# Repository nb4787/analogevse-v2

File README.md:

# analogevse-v2
AnalogEVSE Version 2

A fully analog J1772 compliant EV charge controller. For details go to the home page

http://www.analogevse.xyz

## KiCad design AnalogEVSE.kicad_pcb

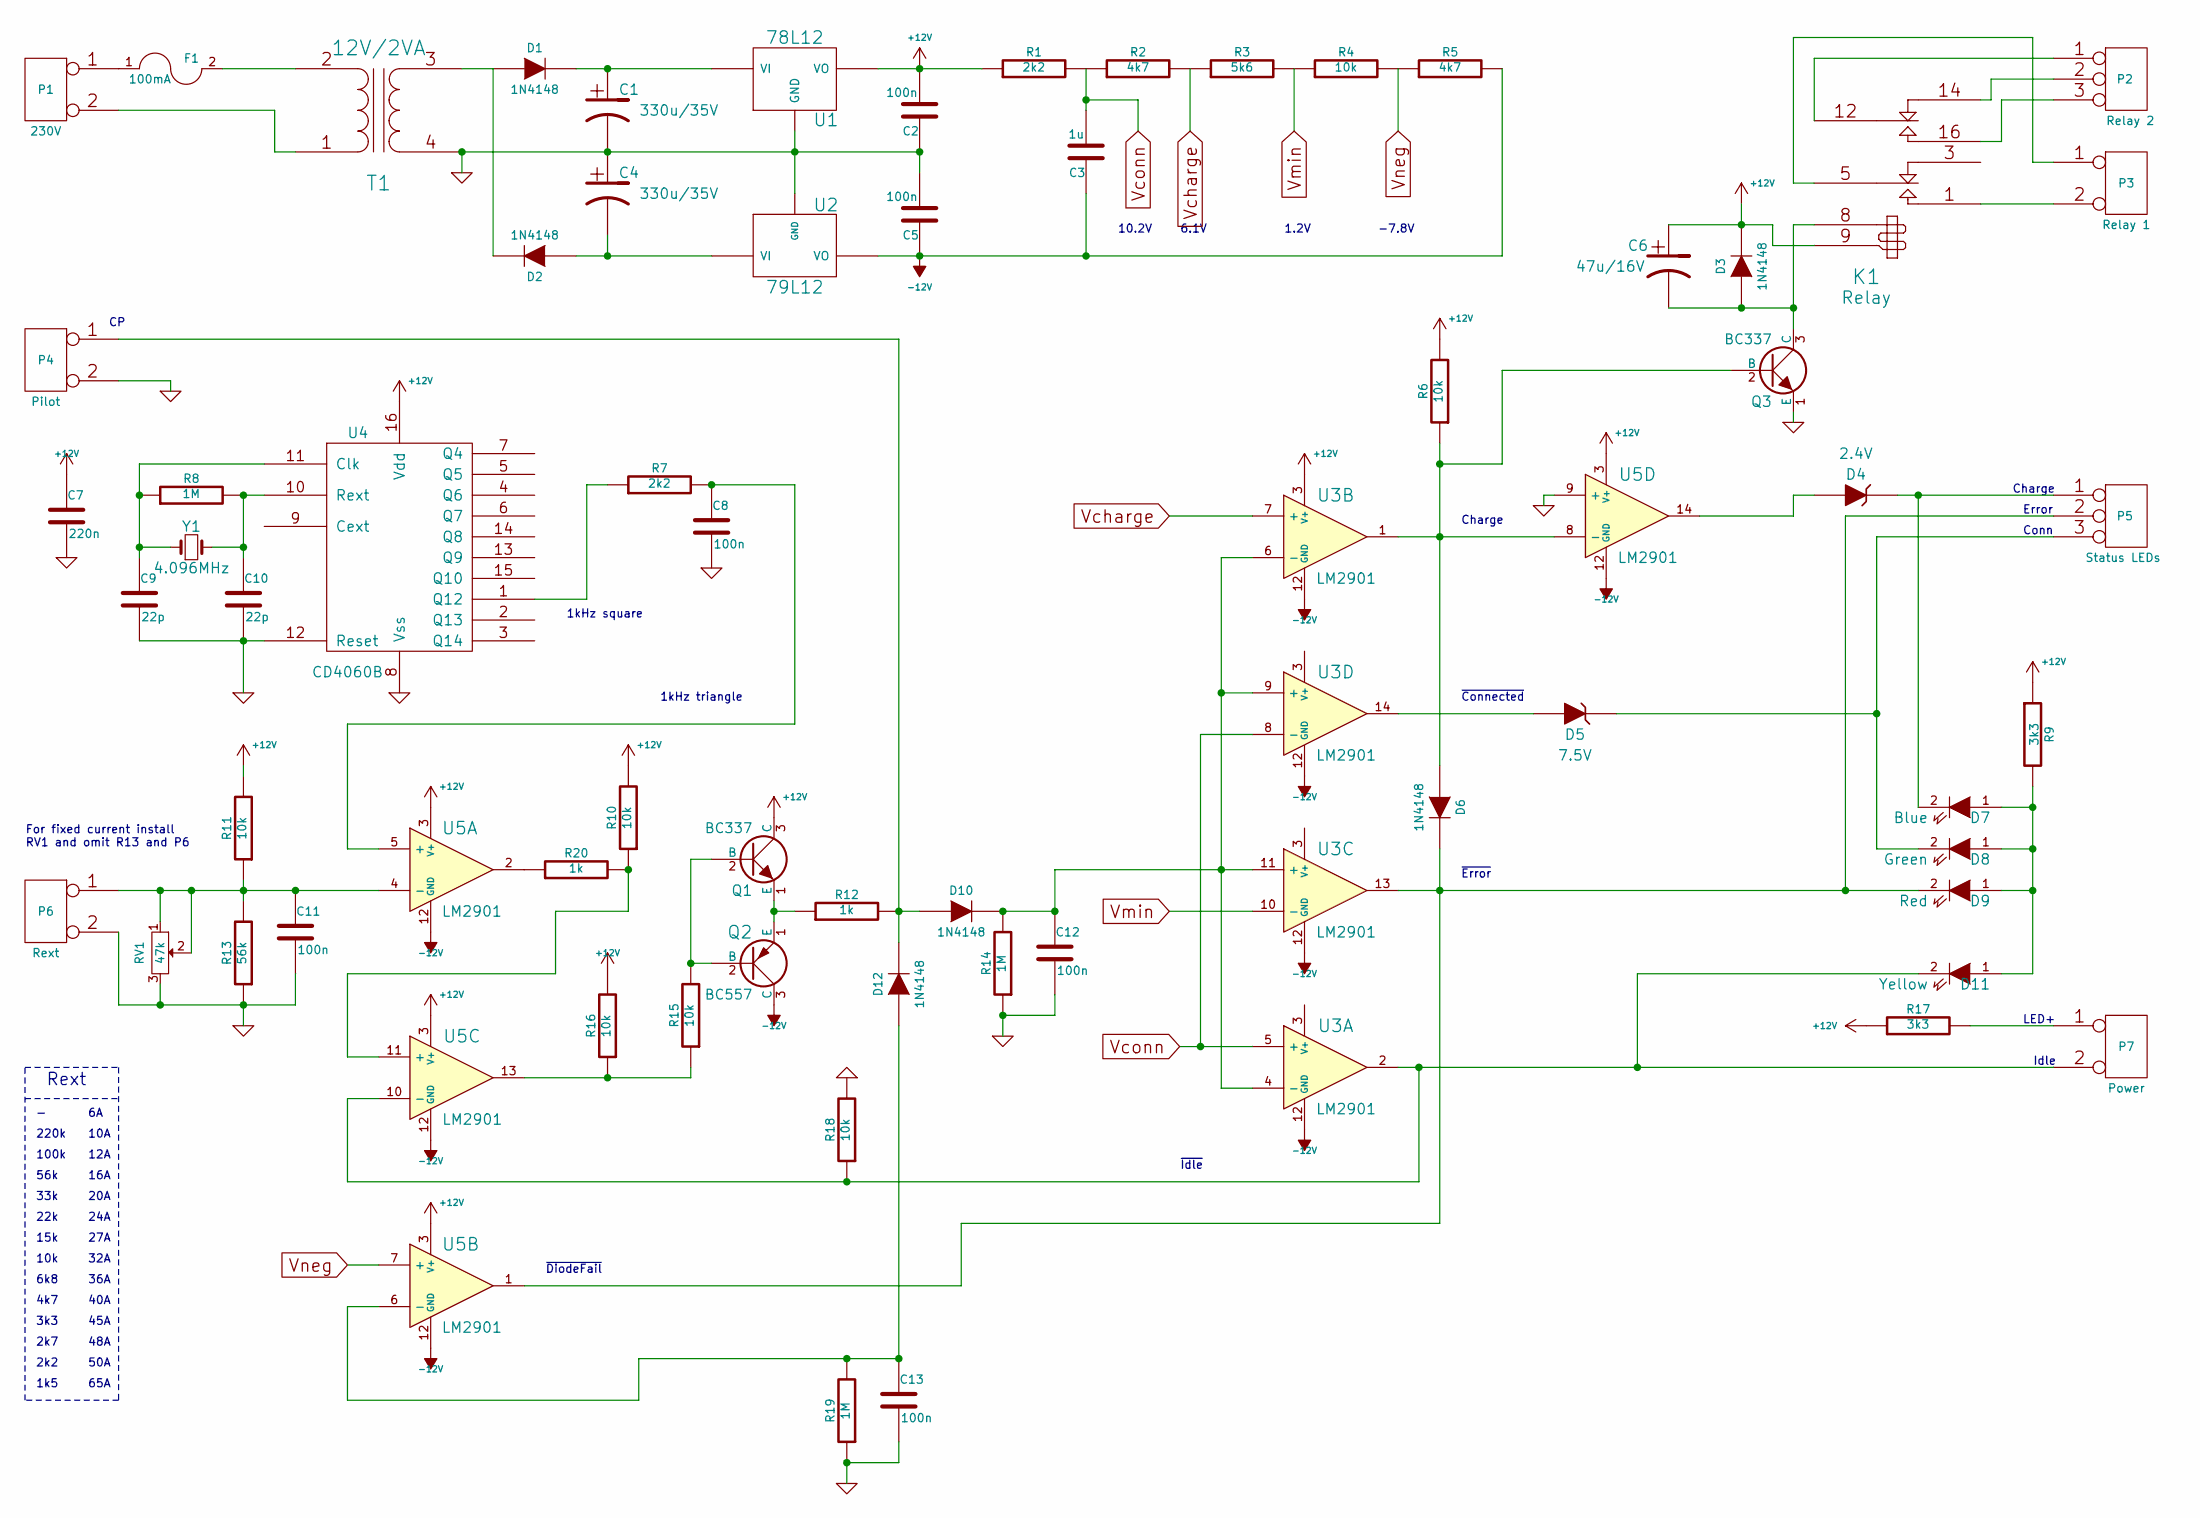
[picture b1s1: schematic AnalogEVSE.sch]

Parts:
C1, C4: 330u/35V; C5
C2, C5, C8, C11, C12, C13: 100n; C2
C3: 1u; C2
C6: 47u/16V; C3-ROUND
C7: 220n; C2
C9, C10: 22p; C2
D1, D2, D3, D6, D10, D12: 1N4148; D3
D4: 2.4V; D3-Zener
D5: 7.5V; D3-Zener
D7: Blue; LED-3
D8: Green; LED-3
D9: Red; LED-3
D11: Yellow; LED-3
F1: 100mA; Fuse-RM9
K1: Relay
P1: 230V; Term-2pin
P2: Relay 2; Term-3pin
P3: Relay 1; Term-2pin
P4: Pilot; Term-2pin
P5: Status LEDs; Term-3pin
P6: Rext; Term-2pin
P7: Power; Term-2pin
Q1, Q3: BC337; TO92
Q2: BC557; TO92
R1, R7: 2k2; R3.5
R2, R5: 4k7; R3.5
R3: 5k6; R3.5
R4, R6, R10, R11, R15, R16, R18: 10k; R3.5
R8, R14, R19: 1M; R3.5
R9, R17: 3k3; R3.5
R12, R20: 1k; R3.5
R13: 56k; R3.5
RV1: 47k; Trimpot3
T1: 12V/2VA; Printtrafo2VA-multi
U1: 78L12
U2: 79L12
U3, U5: LM2901; IC-DIP-14-SHORT
U4: CD4060B; IC-DIP-16
Y1: 4.096MHz; Crystal

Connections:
+12V: C2.2, C6.1, C7.1, D3.2 (K), K1.9, Q1.3 (C), R1.1, R6.2, R9.1, R10.2, R11.2, R16.2, R17.1, U1.VO, U3.3 (V+), U4.16 (Vdd), U5.3 (V+)
-12V: C3.1, C5.1, Q2.3 (C), R5.2, U2.VO, U3.12 (GND), U5.12 (GND)
GND: C1.2, C2.1, C4.1, C5.2, C7.2, C8.2, C9.2, C10.2, C11.2, C12.2, C13.2, P4.2 (PM), P6.2 (PM), Q3.1 (E), R13.1, R14.1, R18.2, R19.1, RV1.3, T1.4 (SB), U1.GND, U2.GND, U4.8 (Vss), U4.12 (Reset), U5.9 (+)
unnamed: C1.1, D1.2 (K), U1.VI
unnamed: C4.2, D2.1 (A), U2.VI
unnamed: C6.2, D3.1 (A), K1.8, Q3.3 (C)
unnamed: C8.1, R7.2, U5.5 (+)
unnamed: C9.1, R8.1, U4.11 (Clk), Y1.1
unnamed: C10.1, R8.2, U4.10 (Rext), Y1.2
unnamed: C11.1, P6.1, R11.1, R13.2, RV1.1, RV1.2, U5.4 (-)
unnamed: C12.1, D10.2 (K), R14.2, U3.4 (-), U3.6 (-), U3.9 (+), U3.11 (+)
unnamed: C13.1, D12.1 (A), R19.2, U5.6 (-)
unnamed: D1.1 (A), D2.2 (K), T1.3 (SA)
unnamed: D4.1 (K), D7.2 (K), P5.1
unnamed: D4.2 (A), U5.14
unnamed: D5.1 (K), D8.2 (K), P5.3
unnamed: D5.2 (A), U3.14
unnamed: D6.1 (A), Q3.2 (B), R6.1, U3.1, U5.8 (-)
unnamed: D6.2 (K), D9.2 (K), P5.2 (PM), U3.13, U5.1
unnamed: D10.1 (A), D12.2 (K), P4.1, R12.2
unnamed: D7.1 (A), D8.1 (A), D9.1 (A), D11.1 (A), R9.2
unnamed: D11.2 (K), P7.2 (PM), R18.1, U3.2, U5.10 (-)
unnamed: F1.1, P1.1
unnamed: F1.2, T1.2 (AB)
unnamed: K1.1 (T1), P3.2 (PM)
unnamed: K1.5 (C1), P3.1
unnamed: K1.12 (C2), P2.1
unnamed: K1.14 (R2), P2.2 (PM)
unnamed: K1.16 (T2), P2.3
unnamed: P1.2 (PM), T1.1 (AA)
unnamed: P7.1, R17.2
unnamed: Q1.1 (E), Q2.1 (E), R12.1
unnamed: Q1.2 (B), Q2.2 (B), R15.2
unnamed: R7.1, U4.1 (Q12)
unnamed: R10.1, R20.2, U5.11 (+)
unnamed: R15.1, R16.1, U5.13
unnamed: R20.1, U5.2
Vcharge: R2.2, R3.1, U3.7 (+)
Vconn: C3.2, R1.2, R2.1, U3.5 (+), U3.8 (-)
Vmin: R3.2, R4.1, U3.10 (-)
Vneg: R4.2, R5.1, U5.7 (+)

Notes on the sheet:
~DiodeFail
Charge
~Connected
~Error
~Idle
Conn
Error
1kHz square
1kHz triangle
Idle
LED+
220k
10A
100k
12A
56k
16A
10k
32A
33k
20A
22k
24A
15k
27A
2k7
48A
6k8
36A
4k7
40A
3k3
45A
1k5
65A
2k2
50A
Rext
For fixed current install RV1 and omit R13 and P6
10.2V

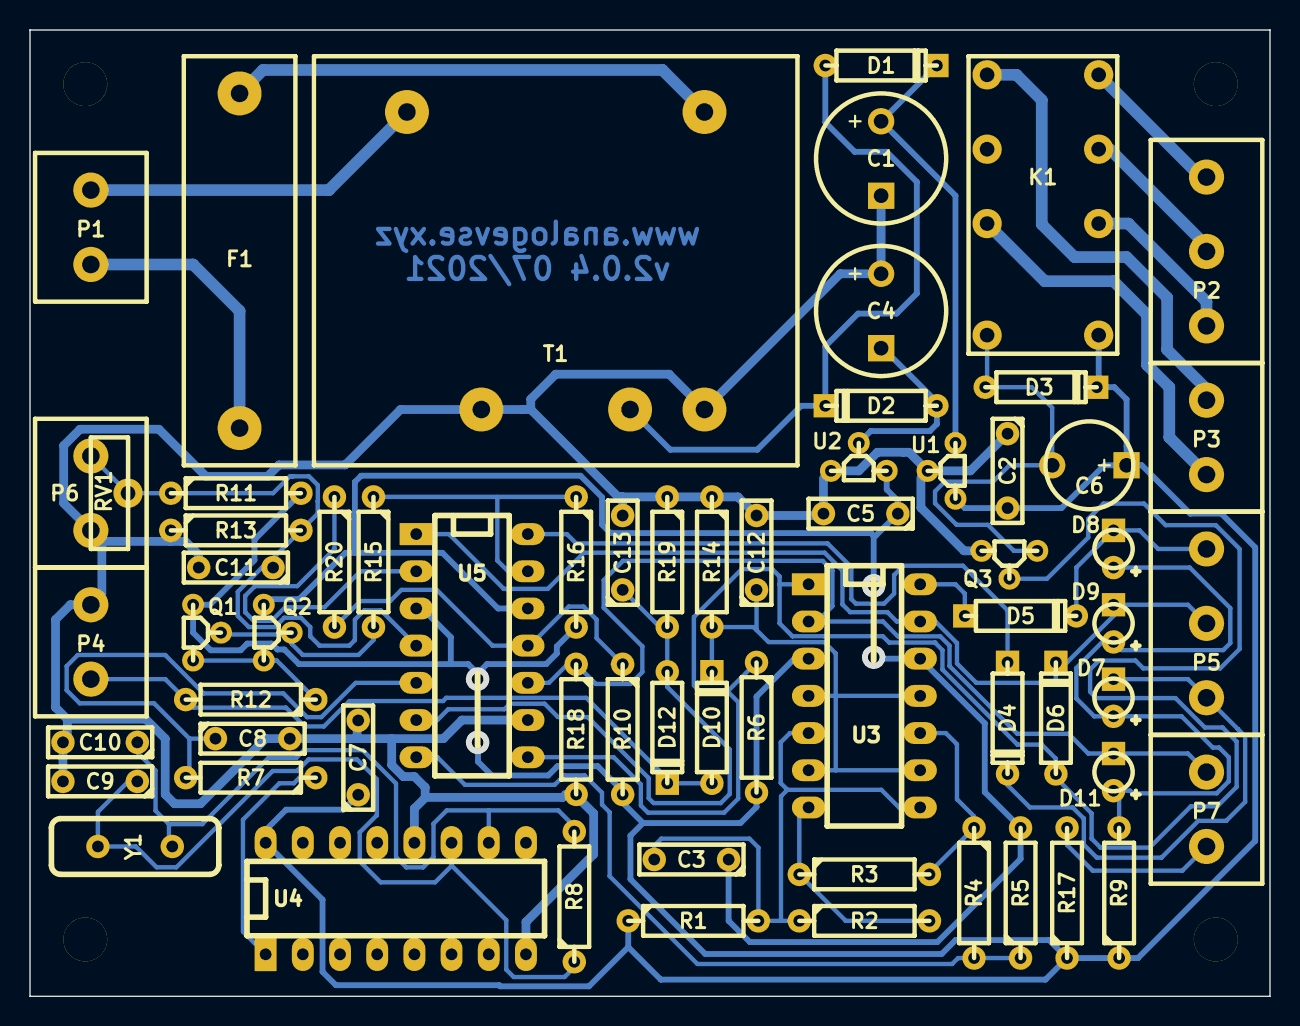
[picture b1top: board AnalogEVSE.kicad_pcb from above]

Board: 2 copper layers, 84.7 x 66.0 mm, 65 parts (0 on the bottom side), 41 nets.

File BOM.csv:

Component;Quantity;Value
C1,C4;2;330u/35V
C2,C5,C8,C11,C12,C13;6;100n
C3,C7;2;220n
C9,C10;2;22p
D1,D3,D6,D2,D10,D12;6;1N4148
F1;1;100mA
K1;1;Relay
P1;1;230V
P2;1;Relay 2
P3;1;Relay 1
P4;1;Pilot
P5;1;Status LEDs
P6;1;Rext
P7;1;Power
Q1,Q3;2;BC337
U1;1;78L12
U2;1;79L12
U4;1;CD4060B
Y1;1;4.096MHz
R1,R7;2;2k2
R2,R5;2;4k7
R3;1;5k6
R4,R6,R10,R11,R15,R16,R18;7;10k
R8,R14,R19;3;1M
R9,R17;2;3k3
R12;1;1k
R13;1;56k
C6;1;47u/16V
D7;1;Blue
D8;1;Green
D9;1;Red
D11;1;Yellow
Q2;1;BC557
D4;1;2.4V
D5;1;7.5V
RV1;1;47k
U3,U5;2;LM2901
T1;1;12V/2VA

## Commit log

2018-12-30 Gerber files for PCB manufacturing
2019-01-03 KiCAD 5, BOM
2019-01-03 PCB order
2019-03-07 Cleanup
2019-05-04 BOM update
2020-04-18 Release 2.0.3
2021-08-08 Version 2.0.4 with R20 for proper +12V when idle
